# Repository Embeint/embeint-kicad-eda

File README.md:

# Embeint KiCad

Embeint KiCad is an Embeint-maintained fork of KiCad for AI-assisted electronic
design. The project aims to make schematic generation and PCB workflows native,
live and inspectable, with first-class Model Context Protocol (MCP) support and a
long-term path to shared Rust engines and WebAssembly applications.

Source and contributions: [Embeint/embeint-kicad-eda](https://github.com/Embeint/embeint-kicad-eda).

This is an independent project built on KiCad. It is not an official KiCad release
and is not endorsed by the KiCad project. KiCad and its contributors provide the
underlying editors, electrical engines and file formats; their attribution and
licenses remain in this repository.

## Project goals

- **AI schematic generation:** create and refine hierarchical schematics through
  the live editor, using real symbols, pins, wires and connectivity. Generated
  designs must be readable, reviewable and checked with KiCad's electrical rules.
- **First-class MCP support:** provide a supported, bundled interface for assistants
  to discover capabilities, inspect the open design and perform explicit, undoable
  edits. Keep the design engine usable across model providers and assistant clients.
- **A dependable desktop application:** package reproducible builds, isolate
  development configuration, test save/reopen behavior and publish clear
  compatibility information before calling a build a supported release.
- **Shared Rust systems:** replace bounded components incrementally behind stable
  interfaces, starting with deterministic layout and design operations. Validate
  each replacement against the existing implementation and native KiCad checks.
- **WebAssembly and browser workflows:** reuse portable Rust components for browser
  viewing and layout previews, then develop interactive editing. Desktop KiCad
  initially remains responsible for native electrical checks and manufacturing
  exports.
- **KiCad compatibility and maintenance:** preserve familiar project and library
  workflows, track upstream changes and qualify updates before promoting releases.

## Current status

This is a development fork. It already includes C++ IPC extensions and a Python
MCP server for live schematic, PCB, symbol and footprint editing; hierarchy and
connectivity inspection; rendering; ERC/DRC; and explicit saves and exports.
Supported item-edit batches use KiCad commits and undo. Some settings operations
have separate limitations, documented by their tools.

The current source identifies as the **10.99 development line**. Compatibility with
KiCad 10.0.6, particularly saving files that 10.0.6 can reopen, has not been qualified.
Use copies of production designs when evaluating the fork.

The bundled Python MCP remains the default. An opt-in Rust MCP server implements
the first discovery/read/edit subset, and a shared Rust layout component has
native/WASM parity checks. Full native MCP parity, release-qualified installers
and a browser editor remain work in progress; see [current Rust MCP evidence](rust/MCP.md).

## Roadmap

1. Establish the Embeint distribution, project identity and release process.
2. Deliver a repeatable desktop schematic-generation workflow with bundled MCP,
   hierarchical fixtures, connectivity checks, undo and save/reopen validation.
3. Port a bounded schematic-layout component to Rust and validate native/WASM parity.
4. Migrate MCP tools to a bundled native executable while preserving their contracts.
5. Deliver browser previews and then interactive editing using the shared components.

See the [engineering roadmap](tools/live_schematic_mcp/EMBEINT_FORK_ROADMAP.md) for
architecture, delivery gates, compatibility requirements and planning assumptions.
The immediate priority is [complete native Rust MCP parity](rust/MCP_PARITY_PLAN.md),
including all Python tools and resources, followed by closing the broader KiCad
function-coverage gaps before browser work. Every operation must execute natively;
forwarding unported tools to Python does not meet this target. The
[desktop support gates](tools/live_schematic_mcp/MCP_SUPPORT_PLAN.md) still apply.

## Build and use the development version

The documented development environment is Windows with WSL Ubuntu. Building KiCad
requires substantial native dependencies; the setup script reports missing system
packages. See the [live MCP setup guide](tools/live_schematic_mcp/README.md) for
prerequisites, client registration and tool reference.

From the repository root in WSL:

```bash
tools/live_schematic_mcp/scripts/setup_wsl.sh
tools/live_schematic_mcp/run_kicad_wsl.sh
```

For a new checkout, clone the Embeint product branch first:

```bash
git clone --branch main https://github.com/Embeint/embeint-kicad-eda.git
cd embeint-kicad-eda
```

Run the launcher in a separate terminal while testing. Use the disposable
`live-demo` project, which is the launcher's default, for live tests:

```bash
tools/live_schematic_mcp/scripts/run_tests.sh
tools/live_schematic_mcp/scripts/run_tests.sh --live
```

The live tests edit the open test document. Do not point them at a production
project. The [agent and developer guide](tools/live_schematic_mcp/AGENTS.md) explains
the code structure, test guard and editor integration requirements.

### Native Windows build

To open and edit projects with the fork as a normal Windows application, build it
natively with Visual Studio ("Desktop development with C++"; tested with Visual
Studio 2026). From the repository root in PowerShell:

```powershell
powershell -ExecutionPolicy Bypass -File tools\live_schematic_mcp\scripts\build_windows.ps1
```

The script clones vcpkg into `C:\kb\vcpkg` and builds into `C:\kb\build`. Use `-Root`
for another location, but keep the path short. It then installs to `C:\kb\install`,
copies the runtime DLLs and links the stock symbol, footprint and 3D libraries from
the newest installed upstream KiCad. It also adds an "Embeint KiCad" Start Menu
shortcut. The first run builds every dependency from source and takes hours; later
runs rebuild only what changed. Pass `-NoConfigure` to skip reconfiguring.

The native build keeps its settings separate from an upstream KiCad install.

The MCP adapter drives the native editor too, over KiCad's local named pipe. Set it up
and start an isolated test instance with:

```powershell
tools\live_schematic_mcp\scripts\setup_windows.ps1      # Python venv in C:\kb\venv and protocol code
tools\live_schematic_mcp\run_kicad_windows.ps1 -Wait    # isolated config, API enabled, disposable live-demo project
tools\live_schematic_mcp\scripts\run_tests.ps1 -Live    # unit and end-to-end tests against it
```

Register `run_mcp_windows.ps1` as the MCP server, or, without Python or this checkout,
the bundled `C:\kb\install\mcp\embeint-kicad-mcp.exe` that `build_windows.ps1` installs
(Python 3.11+ is needed only to build it; `-McpOnly` rebundles it). See
[Setup (native Windows)](tools/live_schematic_mcp/README.md#setup-native-windows) for
details and limits; the WSL build and its scripts work as before.

## Contributing and licensing

Contributions to this fork belong in this repository. Read
[CONTRIBUTING.md](CONTRIBUTING.md) for Embeint's development and AI-assistance
guidelines. Upstream KiCad has its own contribution policies, which apply to work
submitted to upstream KiCad.

The combined KiCad distribution is licensed under **GPLv3 or later**, with component
licenses detailed in [LICENSE.README](LICENSE.README). See [LICENSE](LICENSE),
[AUTHORS.txt](AUTHORS.txt) and the existing source notices for terms and attribution.
Keep corresponding source available for distributed builds.

## Upstream KiCad reference

For specific documentation about [building KiCad](https://dev-docs.kicad.org/en/build/), policies
and guidelines, and source code documentation see the
[Developer Documentation](https://dev-docs.kicad.org) website.

You may also take a look into the [Wiki](https://gitlab.com/kicad/code/kicad/-/wikis/home),
the [contribution guide](https://dev-docs.kicad.org/en/contribute/).

For general information about KiCad and information about contributing to the documentation and
libraries, see our [Website](https://kicad.org/) and our [Forum](https://forum.kicad.info/).

## Build state

KiCad uses a host of CI resources.

GitLab CI pipeline status can be viewed for Linux and Windows builds of the latest commits.

## Release status

## Files
* [AUTHORS.txt](AUTHORS.txt) - The authors, contributors, document writers and translators list
* [CMakeLists.txt](CMakeLists.txt) - Main CMAKE build tool script
* [copyright.h](copyright.h) - A very short copy of the GNU General Public License to be included in new source files
* [Doxyfile](Doxyfile) - Doxygen config file for KiCad
* [INSTALL.txt](INSTALL.txt) - The release (binary) installation instructions
* [uncrustify.cfg](uncrustify.cfg) - Uncrustify config file for uncrustify sources formatting tool
* [_clang-format](_clang-format) - clang config file for clang-format sources formatting tool

## Subdirectories

* [3d-viewer](3d-viewer)         - Sourcecode of the 3D viewer
* [cmake](cmake)      - Modules for the CMAKE build tool
* [common](common)            - Sourcecode of the common library
* [cvpcb](cvpcb)             - Sourcecode of the CvPCB tool
* [demos](demos)             - Some demo examples
* [doxygen](doxygen)     - Configuration for generating pretty doxygen manual of the codebase
* [eeschema](eeschema)          - Sourcecode of the schematic editor
* [gerbview](gerbview)          - Sourcecode of the gerber viewer
* [include](include)           - Interfaces to the common library
* [kicad](kicad)             - Sourcecode of the project manager
* [libs](libs)           - Sourcecode of KiCad utilities (geometry and others)
* [pagelayout_editor](pagelayout_editor) - Sourcecode of the pagelayout editor
* [patches](patches)           - Collection of patches for external dependencies
* [pcbnew](pcbnew)           - Sourcecode of the printed circuit board editor
* [plugins](plugins)           - Sourcecode for the 3D viewer plugins
* [qa](qa)                - Unit testing framework for KiCad
* [resources](resources)         - Packaging resources such as bitmaps and operating system specific files
    - [bitmaps_png](resources/bitmaps_png)       - Menu and program icons
    - [project_template](resources/project_template)          - Project template
* [thirdparty](thirdparty)           - Sourcecode of external libraries used in KiCad but not written by the KiCad team
* [tools](tools)             - Helpers for developing, testing and building
* [translation](translation) - Translation data files (managed through [Weblate](https://hosted.weblate.org/projects/kicad/master-source/) for most languages)
* [utils](utils)             - Small utils for KiCad, e.g. IDF, STEP, and OGL tools and converters

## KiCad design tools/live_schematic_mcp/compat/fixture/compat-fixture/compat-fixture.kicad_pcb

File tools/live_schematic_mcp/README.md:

# Live KiCad MCP

An MCP server that edits the schematic and board **open in KiCad** through the IPC API: no file
edits, no save/reload. Changes appear in the editor immediately, each tool call is one undo step,
and `live_schematic_view` / `live_pcb_view` return PNGs KiCad renders from the in-memory (unsaved)
design.

Requires this development build (10.99 / KiCad 11). Released KiCad 10.x has no schematic IPC.

The proposed path to an Embeint distribution with bundled MCP, shared Rust components
and a browser client is in [Embeint fork roadmap](EMBEINT_FORK_ROADMAP.md).
Desktop MCP reliability and workflow coverage take priority; see the
[MCP support delivery plan](MCP_SUPPORT_PLAN.md) and the
[IPC/MCP review record](IPC_MCP_REVIEW.md).

`live_mcp_capabilities` and the JSON resource `embeint://mcp/capabilities` expose the
loaded MCP tool schemas, curated IPC command schemas and a deterministic schema
fingerprint without connecting to KiCad. This describes the local adapter; it does
not assert that every operation is supported by the running editor or document.
The unit suite also exercises the real MCP stdio initialize/discover/call/resource
protocol, and the `MCP contracts` GitHub workflow runs these checks on pull requests.

Design work uses the bundled [Embeint house style](skills/kicad-house-style/SKILL.md).
MCP initialization instructions direct agents to `live_skill_reference` with
`skill="kicad-house-style"`; the entrypoint links the reference for each task.
With no arguments the tool lists skills, versions and files. Offline resources
provide the same data: `kicad-skill://index`, `kicad-skill://{skill}/{file}` and
`kicad-skill://manifest`. The manifest records raw UTF-8 file SHA-256 hashes and
an aggregate content hash separately from the capability schema fingerprint.
Workstation paths and optional selector configuration stay outside the portable
guidance. Start a new server process/session to receive updated initialization
instructions and bundled content; discovery does not establish live design acceptance.

The editor transport is KiCad's local IPC only: a Unix socket for the WSL/Linux build,
and a local named pipe (`\\.\pipe\<temp>\kicad\api.sock`, URL
`ipc://C:\Users\...\Temp\kicad\api.sock`) for the native Windows build. Run the server
next to the KiCad it drives: inside WSL for the WSL build (through `wsl.exe`), natively
for the native build (see [Setup (native Windows)](#setup-native-windows)). Network
transports, UNC pipes and dot-segment pipe paths are rejected before any request.
Offline tests that create Unix socket peers are skipped on Windows and must also run
inside WSL; the named-pipe tests run only on Windows.

Atomic batches accept only item edits that participate in the current commit.
Settings, file operations, editor replacement and asynchronous work are excluded.
Omitted command document targets inherit the batch document; explicit targets must
match it exactly. Selection and zoom changes are not rolled back. Inspect a command
with `live_schematic_describe_command` to see its `batchable` status.

Concurrent writers and lost replies follow the [revision contract](REVISIONS.md).
Every editor reply carries the document revision, and `live_document_revision` reads it.
The generic edit tools accept an optional `expected_revision`, and KiCad refuses
(`AS_REVISION_MISMATCH`) an edit made against a stale revision before changing
anything. A batch is also rolled back if another writer changes the document while
it runs. Every mutation carries an operation id. After a timeout the client asks
`live_operation_status` instead of resending; mutations are never retried. A
client killed mid-batch has its open commit rolled back when the commit's lease
expires (the MCP asks for 60 s; leases are opt-in, so other API clients keep
upstream behaviour, and time under an API task does not count).

Routing verification checks all clearance, keepout and manufacturing findings for
the new route UUIDs, without truncating the internal DRC report. A rejected route
is removed by its UUIDs in a separate undoable cleanup, preserving unrelated user
edits. A timeout or unconfirmed cleanup reports that the editor needs inspection.
This is scoped route validation, not a claim that the whole board is DRC-clean.

## Tools

| Tool | Purpose |
| --- | --- |
| `live_skill_reference` | Offline bundled Embeint design guidance; no arguments lists skills, `skill=` reads SKILL.md, `file=` selects a linked reference |
| `live_schematic_documents` | Open schematic + KiCad version; returns the document spec other tools take |
| `live_schematic_open` | Open the project's schematic when KiCad runs as the project manager |
| `live_schematic_hierarchy` | Live sheet tree, including unsaved sheets, with UUID sheet paths |
| `live_schematic_items` | Items on one sheet (protobuf JSON, nanometers) |
| `live_schematic_create_items` / `_update_items` / `_delete_items` | Batched edits, one undo step, rolled back on any rejection |
| `live_schematic_place_symbol` | Place `Library:Symbol` at mm coordinates |
| `live_schematic_view` | PNG of the whole page in its current unsaved state, with the drawing sheet (border, title block) unless `frame=false` |
| `live_schematic_page` | Paper and orientation, drawing area, title block box and fields (mm), items outside the border or in the title block (`fits`), and separately overlapping fields, labels, sheet pins, text, bodies and wires through text (`overlap_free`, `overlaps`) |
| `live_schematic_set_page` | Set the paper (A4, A3, ...), orientation and title block fields |
| `live_schematic_focus` | Switch the editor to a sheet and zoom to items |
| `live_schematic_item_schema` | Field reference for item types (SheetSymbol, SheetPin, ...) |
| `live_schematic_save` | Explicit save, only when asked |
| `live_schematic_annotate` | Number references (all / one sheet / listed symbols; by X or Y; first free or sheet x100/x1000) |
| `live_schematic_update_from_library` | Reload symbols from their library, or swap them to another `Library:Symbol` |
| `live_schematic_autoplace_fields` | Re-run field autoplacement on symbols, sheets and labels |
| `live_schematic_move` | Move / rotate / mirror items; attached wires follow and stay square |
| `live_schematic_undo` | Undo or redo the editor's last change |
| `live_document_revision` | Live revision, open API commits and unsaved state of any open document ([contract](REVISIONS.md)) |
| `live_operation_status` | What happened to an edit whose reply was lost (committed, rolled back, rejected, unknown); never resends |
| `live_editor_grid` | Read or set any editor's grid (size, presets, visibility, style, snapping) |
| `live_schematic_symbol_pins` | Placed pins with absolute positions, drawn direction and current net |
| `live_schematic_connect_pins` | Orthogonal wire between two pins (`R1`,`2` to `U1`,`VCC`) |
| `live_schematic_connect_pin_to_net` | Stub wire plus local/global/hierarchical label on a pin |
| `live_schematic_netlist` | Live nets with their `REF.PIN` members across every sheet, and the pins on each sheet path (`scope="sheet"`: pins of the given sheet only) |
| `live_schematic_erc` | Electrical rules check of the unsaved design |
| `live_schematic_select` / `_highlight_nets` | Show items or nets to the user in the editor |
| `live_schematic_export` | SVG, PDF, DXF, PS, netlist or BOM from the unsaved design; the BOM is orderable by default (grouped by value, footprint, manufacturer and MPN, DNP left out), and `options` changes any field of the export job |
| `live_kicad_cli` | Read-only kicad-cli on saved files (ERC, DRC, netlist and other exports) in the environment the running KiCad was launched with; see [kicad-cli](#kicad-cli) for what it refuses |
| `live_schematic_list_commands` / `_describe_command` / `_execute` | Every IPC command KiCad registers, by name |
| `live_schematic_batch` | Several commands as one undo step, all rolled back if any fails |

To change a placed symbol's Value, Footprint or user fields, send back the whole symbol from
`live_schematic_items` with only those fields edited. When its `definition` is returned exactly
as read, the editor keeps the embedded library symbol, its pins and its library link, so ERC
reports no library mismatch. The request's `lib_id` is then ignored as well; change the library
link with `live_schematic_update_from_library` (`new_lib_id`). An edited definition replaces the
embedded symbol. A De Morgan symbol's definition lists only the pins of the placed body style, so
do not edit its definition. Place De Morgan symbols with `live_schematic_place_symbol`: one created
from its full library definition keeps both body styles, but a shape read through the API loses
repeated consecutive polyline vertices, which the stock 74xx and 4xxx gates have, so ERC then
reports a library mismatch.

### Symbol libraries and the Symbol Editor

| Tool | Purpose |
| --- | --- |
| `live_symbol_search` | Search all loaded symbol libraries by name, keywords and description |
| `live_symbol_get` | One library symbol's fields, filters, units and pins |
| `live_symbol_libraries` | Rows of the global and/or project symbol library table |
| `live_symbol_create_library` | New empty `.kicad_sym`, added to the global or project table |
| `live_symbol_register_library` / `_unregister_library` | Add or remove an existing library file in a table |
| `live_symbol_new` / `live_symbol_edit` | Start a new symbol, or open one, in the Symbol Editor (shown live, unsaved) |
| `live_symbol_add_pins` | Pins laid out around a body rectangle on the 2.54 mm grid, from a pin list |
| `live_symbol_set_properties` | Value, footprint, datasheet, description, keywords, filters, user fields (MPN ...) |
| `live_symbol_view` | PNG of the open symbol, including unsaved changes |
| `live_symbol_summary` / `_delete_items` | Pins and shapes of the open symbol; remove items |
| `live_symbol_save` | Write the symbol to its library and reload it, ready for `live_schematic_place_symbol` |

Typical flow: search first; if nothing fits, `live_symbol_create_library` (once), `live_symbol_new`,
`live_symbol_add_pins`, `live_symbol_set_properties`, check with `live_symbol_view`, `live_symbol_save`,
then place it. Pins of multi-unit symbols cannot be assigned to units yet.

Defaults: new symbols get hidden `Manufacturer` and `MPN` fields. Pins follow datasheet convention:
supplies and control inputs on the left, outputs and feedback (ADJ, FB, PG) on the right, grounds
at the bottom. Supplies come first on each side, with two empty rows (7.62 mm, a resistor's pin
spacing) before the signals, so an LDO gets VIN over EN and VOUT over ADJ. The designator sits above
the value at the body's bottom right. Pass sides with `arrange="as_given"` to follow a specific
datasheet pinout exactly.

#### Rust pin layout (opt-in)

`live_symbol_add_pins` lays out pins with `symbol_layout.py`. The Rust port of that layout
([rust/README.md](../../rust/README.md)) can be used instead, opt-in, through
`layout_backend.py`:

| `EMBEINT_LAYOUT_BACKEND` | Effect |
| --- | --- |
| `python` (default) | Python only. The tool result is unchanged. |
| `shadow` | Python lays out the pins; the Rust runner is run as well and compared exactly. A difference is logged and reported, never used. |
| `rust` | The Rust runner lays out the pins. Python is the fallback. |

The runner is the `embeint-layout` binary (`cargo build --release` in `rust/`). When
`EMBEINT_LAYOUT_BIN` is set, it is the only place looked at. Otherwise the runner is looked for next
to a bundled MCP executable, then in `rust/target/release` of this checkout, then in the `PATH`
directories (not the working directory). A runner built from older Rust sources is still used, so rebuild it after
pulling. With `shadow` or `rust`, the tool result gains `layout_backend`: which implementation
produced the layout, plus `fallback` (why Python was used) or `shadow` (`match` or `mismatch`).

The runner is started once per call and exits with it, about 25 ms on Windows: small next to the
IPC round trips of the same tool call. It falls back to Python, and says why, when there is no runner,
it fails or times out (10 s), its output is not a response, or the request is outside its JSON
boundary. Requests that JSON would change (tuples, non-string keys, NaN) stay with Python. A bad pin
list raises the same exception, with the same text, as Python, except for the cases listed under
"Limitations" in [rust/README.md](../../rust/README.md#limitations-and-next-steps), such as the
`repr()` of unassigned code points. `diagnose.py`
reports the setting and the runner it would use under `runtime.layout`.

### Footprints, 3D models and embedded files

| Tool | Purpose |
| --- | --- |
| `live_footprint_search` / `live_footprint_get` | Find footprints by name; read pads, attributes, datasheet and 3D models |
| `live_footprint_libraries` / `_create_library` / `_register_library` / `_unregister_library` | Footprint library tables (global or project); new `.pretty` libraries |
| `live_footprint_new` / `live_footprint_edit` | Start or open a footprint in the Footprint Editor (shown live, unsaved) |
| `live_footprint_generate` | KLC-style footprint from datasheet dimensions: SOIC/TSSOP/MSOP, QFN/DFN (with exposed pad), SOT-23/223, chip 0402-2512, pin headers |
| `live_footprint_set_properties` | Description, keywords, SMD/THT, value, datasheet link, BOM/position exclusions |
| `live_footprint_attach_step` | Embed a STEP/WRL model in the footprint and use it as the 3D model (`kicad-embed://`) |
| `live_embedded_files` / `live_embed_file` / `live_remove_embedded_file` | Files embedded in an open footprint or library symbol |
| `live_footprint_view` / `live_footprint_summary` | PNG of the unsaved footprint; its pads, graphics and texts |
| `live_footprint_save` | Write the footprint to its library and reload it, ready to link from a symbol's Footprint field |

Generated footprints follow the KiCad Library Conventions: pads from the datasheet land pattern
(or IPC-7351 nominal fillets from the lead dimensions), roundrect pads at 25 % (radius at most
0.25 mm), 0.12 mm silkscreen kept 0.2 mm from copper with a pin-1 marker, a 0.10 mm fabrication
outline with a chamfered pin-1 corner and `${REFERENCE}`, and a 0.05 mm courtyard 0.25 mm outside
(0.5 mm for connectors) on a 0.01 mm grid. Datasheets are linked in the Datasheet field, not
embedded; STEP models are embedded so a library carries its own 3D models.

### 3D models from SolidCraft

| Tool | Purpose |
| --- | --- |
| `live_footprint_model_plan` | From the datasheet package drawing: a SolidCraft `batch` (body, gull-wing leads or terminals, pin-1 dimple, colours) and `export` call, in KiCad 3D conventions |
| `live_footprint_view_3d` | KiCad's own 3D render (kicad-cli) of a saved footprint and its models |
| `live_footprint_check_model` | Decode each embedded file, compare it byte for byte with its source, confirm it is the footprint's model, and count the solids KiCad exports when it loads the footprint |

The agent holds both MCP servers and carries the plan across:

1. `live_footprint_generate` the footprint, then `live_footprint_model_plan` with the drawing's A, A1, b, c, E, L
2. SolidCraft MCP: run `solidcraft.arguments` with `batch`, check it with `screenshot`/`measure`, run `export`
3. `live_footprint_attach_step` with the exported file (a Windows path is translated for KiCad in WSL),
   `live_footprint_save`, then `live_footprint_view_3d` and `live_footprint_check_model`

Model conventions: millimetres, origin on the footprint origin at the board's top surface, +Z up,
+X as the footprint, +Y as the footprint's -Y (pin 1 top-left in KiCad sits at model x<0, y>0).
Plans cover gull-wing packages (SOIC/TSSOP/MSOP/SSOP, SOT-23/223), QFN/DFN and chip parts.

Give SolidCraft's MCP a folder on the Windows drive both programs can reach (the plans default to
`%USERPROFILE%\kicad-models`, or set `KICAD_LIVE_MODEL_DIR`):

```bash
claude mcp add solidcraft -- solidcraft-cli mcp --allow-path C:\Users\<you>\kicad-models
```

The Footprint Editor lives in pcbnew; the footprint tools ask the schematic editor to open it
(`OpenFootprintEditor`), which loads pcbnew's code into the running process.

### PCB editor

KiCad must run as the project manager (`run_kicad_wsl.sh project.kicad_pro`, the default), which
hosts the schematic and PCB editors in one process; `live_pcb_open` opens the project's board
(creating it if needed) and returns the board document the other tools take.

| Tool | Purpose |
| --- | --- |
| `live_pcb_open` / `live_pcb_documents` | Open the project's board in the PCB editor; list open boards |
| `live_pcb_summary` / `live_pcb_footprints` / `live_pcb_nets` | Outline, layer count, item counts, footprints (with pads and nets), nets and net classes |
| `live_pcb_update_from_schematic` | Update PCB from Schematic using the schematic's live netlist (dry run available) |
| `live_pcb_place_footprint` / `live_pcb_move` | Place a library footprint; move, rotate, flip and lock footprints by reference |
| `live_pcb_route` / `live_pcb_route_net` | Routes around other nets' copper (with net class clearances), keepouts (also inside footprints) and the board edge, changing layer through vias if allowed; checked by KiCad's DRC and undone if a rule breaks |
| `live_pcb_check_path` / `live_pcb_add_tracks` / `live_pcb_add_via` | Test a proposed track for conflicts; draw tracks (refused if they cross or crowd other nets); vias (net class sizes by default) |
| `live_pcb_outline` | Board outline on Edge.Cuts: rectangle, rounded rectangle or polygon |
| `live_pcb_add_zone` / `live_pcb_add_keepout` / `live_pcb_refill_zones` | Copper pours that follow the outline; keepouts by points or around a footprint (antennas); refill |
| `live_pcb_add_graphics` | Lines, arcs, rectangles, circles, polygons and text on any layer |
| `live_pcb_items` / `_create_items` / `_update_items` / `_delete_items` / `_item_schema` | Raw board items (protobuf JSON), one undo step per call |
| `live_pcb_delete_routing` | Rip up tracks and vias by net and/or layer |
| `live_pcb_view` / `live_pcb_view_3d` | PNG of chosen layers on the page with the drawing sheet; KiCad's 3D render |
| `live_pcb_page` / `live_pcb_set_page` | Page check (drawing area, title block, board outline, items outside the border, overlapping silkscreen/fab text); paper and title block |
| `live_pcb_origins` | Read or set the grid origin and the drill/place origin |
| `live_pcb_layers` | Copper layer count (through the stackup, refused if a removed layer has items), visible and active layers |
| `live_pcb_stackup` / `live_pcb_set_stackup` | Read or change the stackup: layer count, copper and dielectric thickness, core/prepreg, epsilon_r, loss tangent, board thickness, colours, finish |
| `live_pcb_design_rules` / `live_pcb_custom_rules` | Built-in constraints, predefined track widths and via sizes, DRC severities; custom `.kicad_dru` rules |
| `live_pcb_netclasses` | Default track width, clearance and via size per net class, and net assignments |
| `live_pcb_impedance_width` / `live_pcb_rf_net` | Controlled-impedance width (microstrip, CPWG) from the stackup; RF/antenna net class, assignment and isolation rule |
| `live_pcb_drc` / `live_pcb_check` | Design rules check; the same grouped as clearance, keepout, silkscreen, courtyard, connectivity, manufacturing, schematic |
| `live_pcb_select` / `live_pcb_focus` / `live_pcb_undo` | Show footprints or items in the editor; undo and redo |
| `live_pcb_export` | Gerbers, drill, position, STEP, PDF, SVG, DXF, IPC-2581, IPC-D-356, ODB++, DSN and more from the live board; `options` sets any field of the export job (units, formats, layers, origins) |
| `live_pcb_fab_package` | The manufacturing package in `<project>/Outputs`: refuses unsaved designs and DRC errors, exports Gerbers and drill (with a Gerber zip), placement CSV, orderable BOM, schematic and assembly PDFs and STEP (IPC-2581, ODB++ and IPC-D-356 on request), checks them (copper layers, holes, placements against the BOM, missing MPNs) and writes a manifest |
| `live_pcb_save` | Explicit save, only when asked |

`live_schematic_execute` and `live_schematic_batch` also take every board command (see
`live_schematic_list_commands`); supported transactional edits in a batch on one
board document form one undo step.

Hierarchy: create a `SheetSymbol` (with `pins`) on the parent, read its path from
`live_schematic_hierarchy`, then target the child sheet with that `sheet_path` to add matching
`HierarchicalLabel`s.

KiCad commands this fork adds for the tools above (`api/proto/schematic/schematic_commands.proto`):
`AnnotateSchematic`, `UpdateSymbolsFromLibrary`, `AutoplaceFields`, `TransformItems`,
`GetSymbolPins`, `NewLibrarySymbol`, `EditLibrarySymbol`,
`SetLibrarySymbolProperties`, `RenderLibrarySymbol`, `OpenFootprintEditor`, `NewLibraryFootprint`,
`EditLibraryFootprint`, `SetLibraryFootprintProperties`, `RenderLibraryFootprint` and
`EmbedFileFromPath` / `GetEmbeddedFileList` / `RemoveEmbeddedFile`; it also implements the library table and
search commands KiCad declared but left unimplemented (`GetLibraryTable`, `Add`/`Update`/
`DeleteLibraryTableEntry`, `SearchLibraries`). Every editor (schematic, symbol, PCB, footprint)
shares `UndoLastChange` / `RedoLastChange`, `GetPageLayout` and `GetGridSettings` /
`SetGridSettings` (`api/proto/common/commands/editor_commands.proto`), and the project manager
answers `OpenDocument` for the project's schematic and board. For boards it adds `TransformBoardItems` (move, rotate, flip and lock in place) and implements
`UpdateBoardStackup`, which KiCad declares but leaves unimplemented. Transactional item-edit
commands join an open `BeginCommit`, so a supported batch is one undo step. Settings
operations have separate effects and are excluded from batches. Undo/redo need the
GUI and refuse an open commit.

## For agents

Start with [AGENTS.md](AGENTS.md): branch policy, where each command lives, build and test
commands, and the library conventions the tools follow.

## Setup (Windows + WSL Ubuntu)

For the native Windows build see [Setup (native Windows)](#setup-native-windows).

`scripts/setup_wsl.sh` does everything below in one go (and is safe to rerun after a pull);
`scripts/rebuild.sh` rebuilds after C++ edits; `scripts/run_tests.sh [--live]` runs the tests.

```bash
# in WSL, once
python3 -m venv ~/kicad-live/venv
~/kicad-live/venv/bin/pip install -r requirements.txt
~/kicad-live/venv/bin/python generate_proto.py

cmake -S <source> -B ~/kicad-live/build -G Ninja -DCMAKE_BUILD_TYPE=Release \
      -DKICAD_BUILD_QA_TESTS=OFF -DCMAKE_INSTALL_PREFIX=$HOME/kicad-live/install
ninja -j 8 -C ~/kicad-live/build && ninja -j 8 -C ~/kicad-live/build install

./run_kicad_wsl.sh            # isolated config, IPC server enabled, project manager with a demo project
```

Keep the build to 8 jobs: each KiCad compile job can take about 1 GB, and one job per core can
exhaust WSL's memory and kill other work on the machine. `scripts/setup_wsl.sh` and
`scripts/rebuild.sh` read the limit from `KICAD_BUILD_JOBS` (default 8).

`run_kicad_wsl.sh` keeps its settings in `~/kicad-live/config` and reuses the symbol and
footprint libraries from the Windows KiCad 10.0 install.

Register the MCP server (it must run inside WSL, where KiCad's Unix socket lives):

```bash
claude mcp add kicad-live -- wsl.exe -d Ubuntu -- bash /mnt/c/<fork>/tools/live_schematic_mcp/run_mcp_wsl.sh
```

## Setup (native Windows)

For the native Windows build (`scripts/build_windows.ps1`, installed in `C:\kb\install`), the
MCP runs in native Python next to KiCad and talks to its named pipe. From the repository root
in PowerShell (`powershell -ExecutionPolicy Bypass -File <script>` if scripts are blocked):

```powershell
tools\live_schematic_mcp\scripts\setup_windows.ps1       # once, and after pulls: venv in C:\kb\venv, protocol code
tools\live_schematic_mcp\run_kicad_windows.ps1 -Wait     # isolated config, API enabled, project manager with live-demo
tools\live_schematic_mcp\scripts\run_tests.ps1 -Live     # unit tests, then the end-to-end tests against that KiCad
tools\live_schematic_mcp\run_kicad_windows.ps1 -Stop     # stops only the KiCad the launcher started
```

`run_kicad_windows.ps1` keeps its settings in `C:\kb\live\config` (never the Start Menu
build's or upstream KiCad's), creates the disposable test project in
`C:\kb\live\projects\live-demo` (`-Fresh` recreates it) and uses the stock libraries that
`build_windows.ps1` linked from upstream KiCad. `-Project <file>` opens another project or a
`.kicad_sch` (schematic editor only). `KICAD_WINDOWS_ROOT` moves `C:\kb`; `KICAD_LIVE_PYTHON`
selects another interpreter. Python 3.11+ (64-bit) is needed; the launcher uses it too.

Only one KiCad on a Windows account can serve the API: the pipe name is fixed and a second
instance runs without an API. The launcher refuses to start while another KiCad with the API
enabled holds the pipe (in either spelling of the temporary directory), so the MCP cannot
reach the wrong instance. Pipes are found by name; their owner is not verified, so use the
MCP where you trust the machine's other local accounts. For your own KiCad, enable
the API in Preferences > Plugins (Enable KiCad API). The MCP finds the pipe in your temporary
directory; to name an instance explicitly, set `KICAD_API_SOCKET` to the exact endpoint
`scripts\wait_ready.ps1` prints (pipe names are literal: `C:\Users\LONGNA~1\...` and
`C:\Users\LongName\...` are different pipes). `python diagnose.py --probe` lists and probes
the candidates. `KICAD_API_TIMEOUT_MS` sets how long a request waits for its reply (1 to 600000 ms,
default 15000). A lost reply is never resent: edits are reconciled as described in REVISIONS.md.

A native Rust server with the same names and results for discovery, the read-only document tools
and `live_schematic_create_items` is in `rust/` ([rust/MCP.md](../../rust/MCP.md)). It is compared
with this server, which stays the reference and provides every tool.

Register the MCP server (stdout carries only MCP messages):

```powershell
claude mcp add kicad-live -- powershell -NoProfile -ExecutionPolicy Bypass -File C:\<fork>\tools\live_schematic_mcp\run_mcp_windows.ps1
```

### Bundled MCP (no Python, no checkout)

`build_windows.ps1` also installs the MCP as `C:\kb\install\mcp\embeint-kicad-mcp.exe`: the
server frozen with PyInstaller (`qualification\package_mcp.py`), with its own Python runtime,
protocol code, skills and licence notices (`licenses\`). Users of the install need neither
Python nor this repository; 64-bit Python 3.11+ is needed only to build it (`-McpPython` picks the
interpreter and recreates the build environment in `C:\kb\build\mcp\venv`; the script checks it
before compiling). `-McpOnly` rebundles an existing install after an MCP change and `-NoMcp` skips
it. The new package replaces `install\mcp` as a whole: while an MCP client runs the bundled server,
the script refuses and leaves the installed package untouched; close that client and run it again.
Register it directly:

```powershell
claude mcp add kicad-live -- C:\kb\install\mcp\embeint-kicad-mcp.exe
```

```powershell
C:\kb\install\mcp\embeint-kicad-mcp.exe --version            # server and KiCad versions, schema fingerprint
C:\kb\install\mcp\embeint-kicad-mcp.exe --diagnose [--probe]  # runtime, discovered editors, read-only probes
```

The same identity is in `live_mcp_capabilities` (`server_version`, `application_version`,
`source_revision`, `schema_sha256`) and the MCP `serverInfo`. With no editor running, every
editor tool answers at once that no KiCad is listening and what to start; nothing is sent, and
the next call looks again, so the MCP may start before KiCad.

Paths in tool arguments are as the native KiCad reads them (`C:\...`); WSL `/mnt/c/...` paths
are translated. SolidCraft exports default to `%USERPROFILE%\kicad-models`
(`KICAD_LIVE_MODEL_DIR` overrides it).

## Tests

```bash
~/kicad-live/venv/bin/python -m pytest test_client.py      # protocol contracts, no KiCad needed
~/kicad-live/venv/bin/python e2e_smoke.py out/             # against a running editor; never saves
~/kicad-live/venv/bin/python e2e_features.py out/          # annotate, wiring, move, undo, ERC, batch, export
~/kicad-live/venv/bin/python e2e_symbols.py out/           # search, build, save, register and place a symbol
~/kicad-live/venv/bin/python e2e_footprints.py out/        # generate a footprint, embed its STEP, link it from a symbol
~/kicad-live/venv/bin/python e2e_pcb.py out/               # board page, grid, origins, outline, footprints, routing, zones, DRC, exports
~/kicad-live/venv/bin/python e2e_design.py out/            # stackup, impedance, rules, custom rules, net classes, keepouts, routing around copper, checks
~/kicad-live/venv/bin/python e2e_design_checks.py out/     # hierarchical netlist, page text overlaps, kicad-cli in KiCad's environment
~/kicad-live/venv/bin/python e2e_revisions.py out/         # revisions, stale-edit refusal, concurrent clients, lost replies, killed client
SOLIDCRAFT_CLI=/path/to/solidcraft-cli ~/kicad-live/venv/bin/python e2e_model_handoff.py out/     # SolidCraft builds the STEP; KiCad embeds and renders it
~/kicad-live/venv/bin/python e2e_item_roundtrip.py out/    # unchanged item updates and re-creations leave the saved file unchanged
```

On native Windows, `scripts\run_tests.ps1 [-Live]` runs the same set with `C:\kb\venv`
(output in `C:\kb\live\test-output`); run single scripts with `C:\kb\venv\Scripts\python.exe`.

### Item round trip

`e2e_item_roundtrip.py` sends every item back exactly as `GetItems` returned it, and also
deletes it and creates it again from that message. Each time it compares the document saved to a
string (`SaveDocumentToString`, KiCad's own writer) block by block. The default run builds one item
of every schematic type with non-default values far off the test schematic's page and removes it
afterwards; it never saves. `--isolated` (with `KICAD_ROUNDTRIP_ISOLATED=1` and an explicit
`KICAD_API_SOCKET`) runs on a disposable project made by `e2e_item_roundtrip.py prepare <dir>` (qa's
`api_kitchen_sink` schematic and board): it checks every schematic and board item, then saves,
reverts to the saved files and compares every item again.

An update applies the message over the existing item, so whatever the message cannot carry keeps
its value. Fields the message does carry are applied as sent, so send back what you read: an empty
one clears its value (a text box sent without its hyperlink loses it). A definition-less symbol
update keeps the symbol's embedded definition, pins and library link, even if its `lib_id` names
another symbol. Values the files cannot hold are applied as they will be saved, or not at all:

| Field | Behaviour |
| --- | --- |
| `NoConnectMarker.size`, `DirectiveLabel.symbol_size` | Read-only: not saved, every item has the default size |
| Colours | Schematic items, strokes, fills, net classes and stackup layers: applied with 8 bits per channel (as saved). A footprint's extruded 3D body colour is kept at full precision (as saved). Alpha is always kept |
| Text `multiline` | Not saved: each text type keeps its own setting |
| `SheetSymbol.border_stroke.style` | Sheet borders are always solid |
| `SchematicImage.opacity` | Optional: absent means opaque for a new image and unchanged for an update |
| `SchematicImage.transform_origin_offset` | Not saved; reopening resets it |
| Bus-to-bus `BusEntry` | Saved as the bus segment it draws (same UUID); it reopens as a bus line |
| Schematic polyline `closed` | Not saved: polylines reopen open (filled ones still draw closed) |
| `fields_autoplaced` of a label without fields | Not saved |
| Global label intersheet reference visibility | Follows the schematic's setting when loaded |
| Pins and graphics of a symbol definition, pad primitives, the board's own UUID | Have no saved UUID, so they are new after reopening |

Creating an item renews the UUIDs of its children (symbol and sheet pins, table cells), and a
created symbol lists its pins in the order of the request. Sending a symbol with its full
definition keeps the cached library symbol when the definition is unchanged and rebuilds it when it
was edited (see the note after the schematic tools table); the probe reports full-definition results separately
(informational) and checks the instance round trip with a definition-less update.

### kicad-cli

kicad-cli is a separate KiCad process and needs the launcher's environment: the shared library
path, the configuration home (library tables, path variables) and the stock library directories.
The MCP asks the running KiCad for that environment (`GetKiCadEnvironment`) whenever it starts
kicad-cli (`live_kicad_cli`, `live_footprint_view_3d`, `live_footprint_check_model`); with an older
KiCad, or none running, it rebuilds it from the install layout (`run_kicad_wsl.sh` for
`~/kicad-live`, `libexec/environment.sh` for the package; `KICAD_CLI` selects another binary).
From a shell, the installed package provides `embeint-kicad-cli`, which sources the same
environment as `embeint-kicad`.

`live_kicad_cli` only runs commands that read the saved design: `sch erc`, `sch export <kind>`,
`pcb drc`, `pcb export <kind>`, `sym export svg`, `fp export svg` and `version`. It refuses
everything else before starting a process, including `jobset run` (a jobset's "Execute Command"
jobs run through a shell), `upgrade` and `downgrade` (they rewrite files in place) and imports. It
also refuses `pcb drc --save-board`, combined short options such as `-no` (they can hide an
output), and any output (`-o`, `--output`, `--output=...`, `--models-dir`, `--report-path`) that
names a `.kicad_sch`, `.kicad_pcb`, `.kicad_pro`, `.kicad_prl`, `.kicad_sym`, `.kicad_mod` or
`.kicad_dru` file or a library table, or lies inside a `.pretty` folder. On WSL, Windows paths
are translated, including `--option=C:\...`. The tool runs kicad-cli without blocking the MCP
server. `timeout_s` is at most 600 s, and kicad-cli is stopped when it runs out or the call is
cancelled. The MCP falls back to the install layout only when no KiCad can be found or reached.
Other errors from KiCad are reported, and so is an empty environment report (as the note
`KiCad reported an empty launch environment`). A frozen MCP looks for kicad-cli in `../bin` on
Windows (`C:\kb\install\mcp` -> `C:\kb\install\bin`) and in `../../bin` for the Linux package.

### Page overlap check: known limitation

`live_schematic_page` and `live_pcb_page` list at most 200 overlapping pairs. Any pairs beyond those
are counted in `overlaps_not_listed`. The editor currently stores and sorts every pair before it applies that cap. On a
pathological page with many stacked texts, the check can therefore be slow and use a lot of
memory. Keeping only the first 200 pairs while it searches is a planned follow-up.

## Supported schematic block scripting

The source distribution provides `block_helpers.py` for small generated blocks and
UUID-scoped revisions through the existing Python client. Start with
`python tools/live_schematic_mcp/block_example.py` for an offline synthetic plan,
or read the bundled [helper API reference](skills/kicad-house-style/block-helpers.md).
Stable ownership manifests, stale-state fingerprints and single-use plans preserve
manual items and avoid blind mutation replay. Because KiCad's connectivity cleanup
could merge wires or drop junctions, planning refuses block wires touching manual
wiring, removing a block wire or moving/removing a block pin or label with manual
wiring attached, and moving a pin at a wire branch in one apply; wires are replaced
rather than updated. Build wires, junctions, symbols and sheets with `wire()`,
`symbol()` and `sheet()`, not `add()`. Manifests are version 2; version 1 manifests
lack pin points and are refused. This is a scripting API; no new MCP
helper execution tool is registered. Fingerprints do not provide atomic editor
revision checks, and live use requires a single writer plus pin/net/page validation.

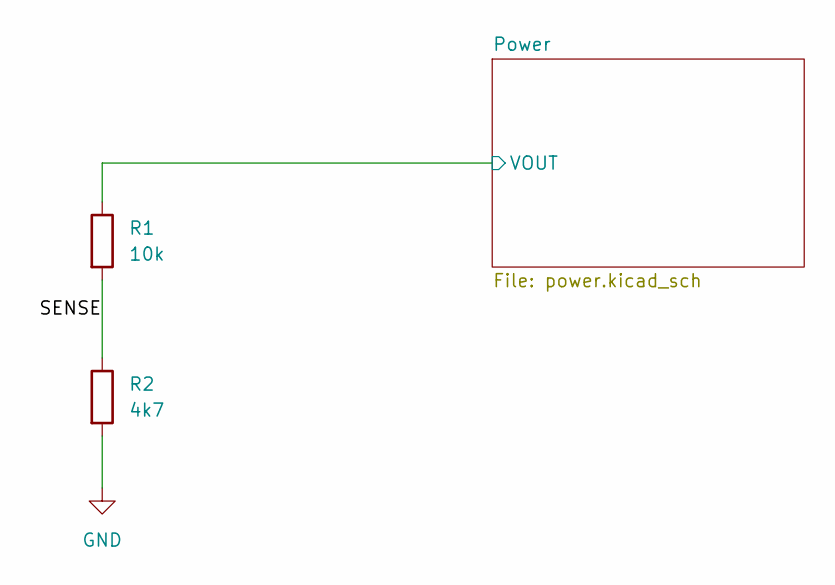
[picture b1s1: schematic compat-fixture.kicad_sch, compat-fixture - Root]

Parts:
R1: 10k; R_0603_1608Metric
R2: 4k7; R_0603_1608Metric

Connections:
/Power/VOUT: R1.1; also elsewhere on the board
/SENSE: R1.2, R2.1
GND: R2.2; also elsewhere on the board

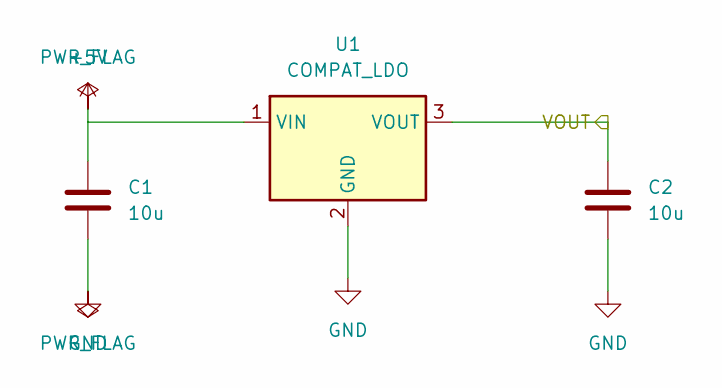
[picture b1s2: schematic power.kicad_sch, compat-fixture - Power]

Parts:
C1, C2: 10u; C_0603_1608Metric
U1: COMPAT_LDO; SOT-23_COMPAT; MPN COMPAT-LDO-33

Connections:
+5V: C1.1, U1.1 (VIN)
/Power/VOUT: C2.1, U1.3 (VOUT); also elsewhere on the board
GND: C1.2, C2.2, U1.2 (GND); also elsewhere on the board

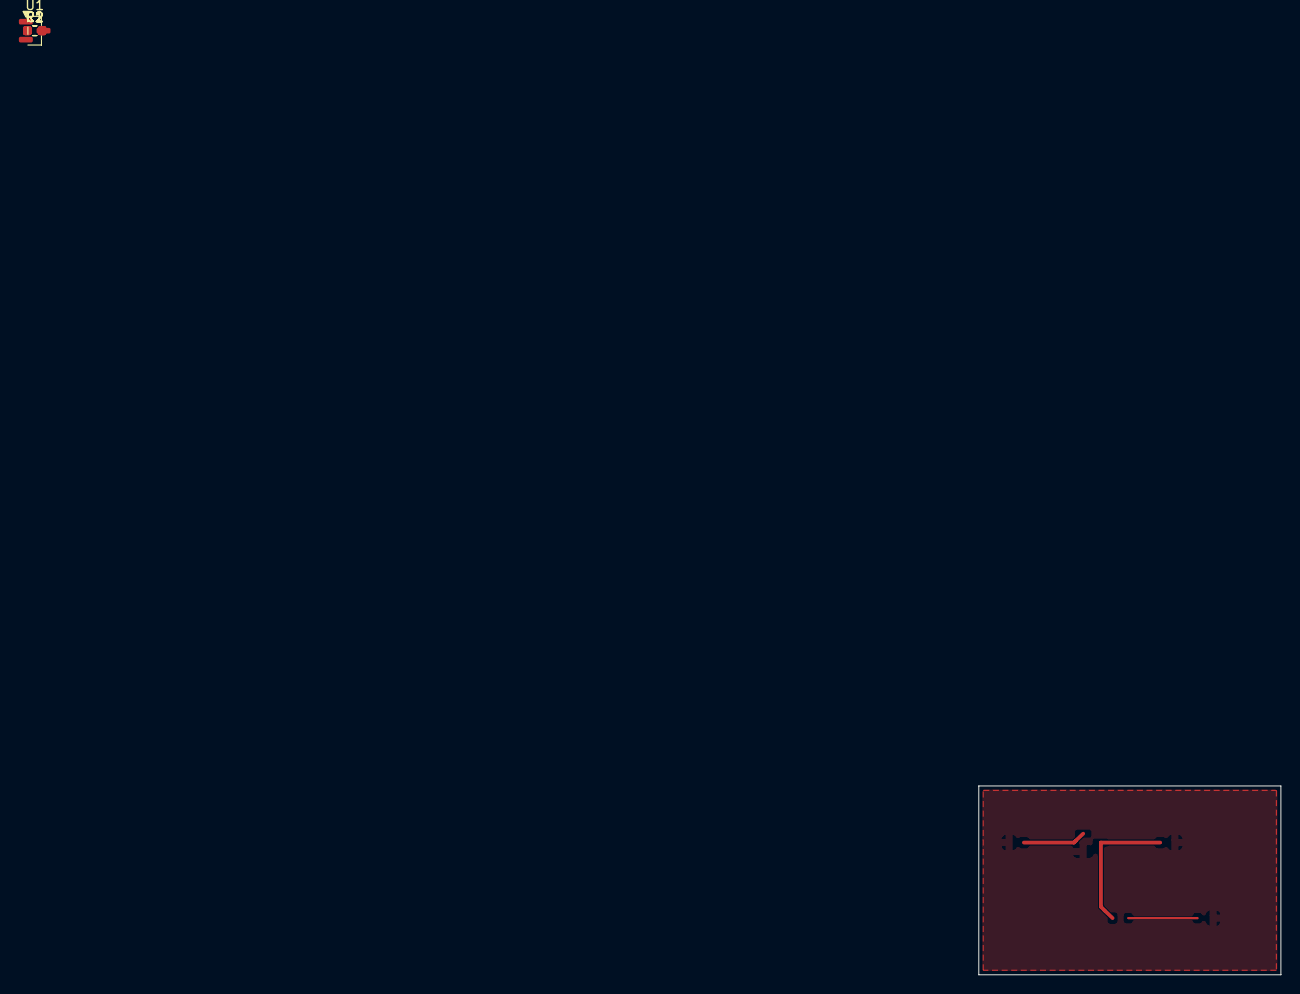
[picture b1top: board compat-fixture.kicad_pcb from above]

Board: 2 copper layers, 32.0 x 20.0 mm, 5 parts (0 on the bottom side), 4 nets.
